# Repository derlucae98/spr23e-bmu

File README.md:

# spr23e-bmu
Disclaimer: This project is free to use. However, if you plan to use it at an official Formula Student event you have to clearly state the origin of the project in your presentation of the Engeneering Design Event! This project contains lethal voltages. You use this project at your own risk! Neither I nor the Scuderia Mensa will take any responsibility in case of damage, fire, injury or death.

Battery Management Unit for the Scuderia Mensa SPR23e/SPR24e electric race car.

REV B has been successfully tested. Rendering: 

The documentation is still in progress and far from finished. Firmare can be found here: https://github.com/derlucae98/spr-bmu-firmware

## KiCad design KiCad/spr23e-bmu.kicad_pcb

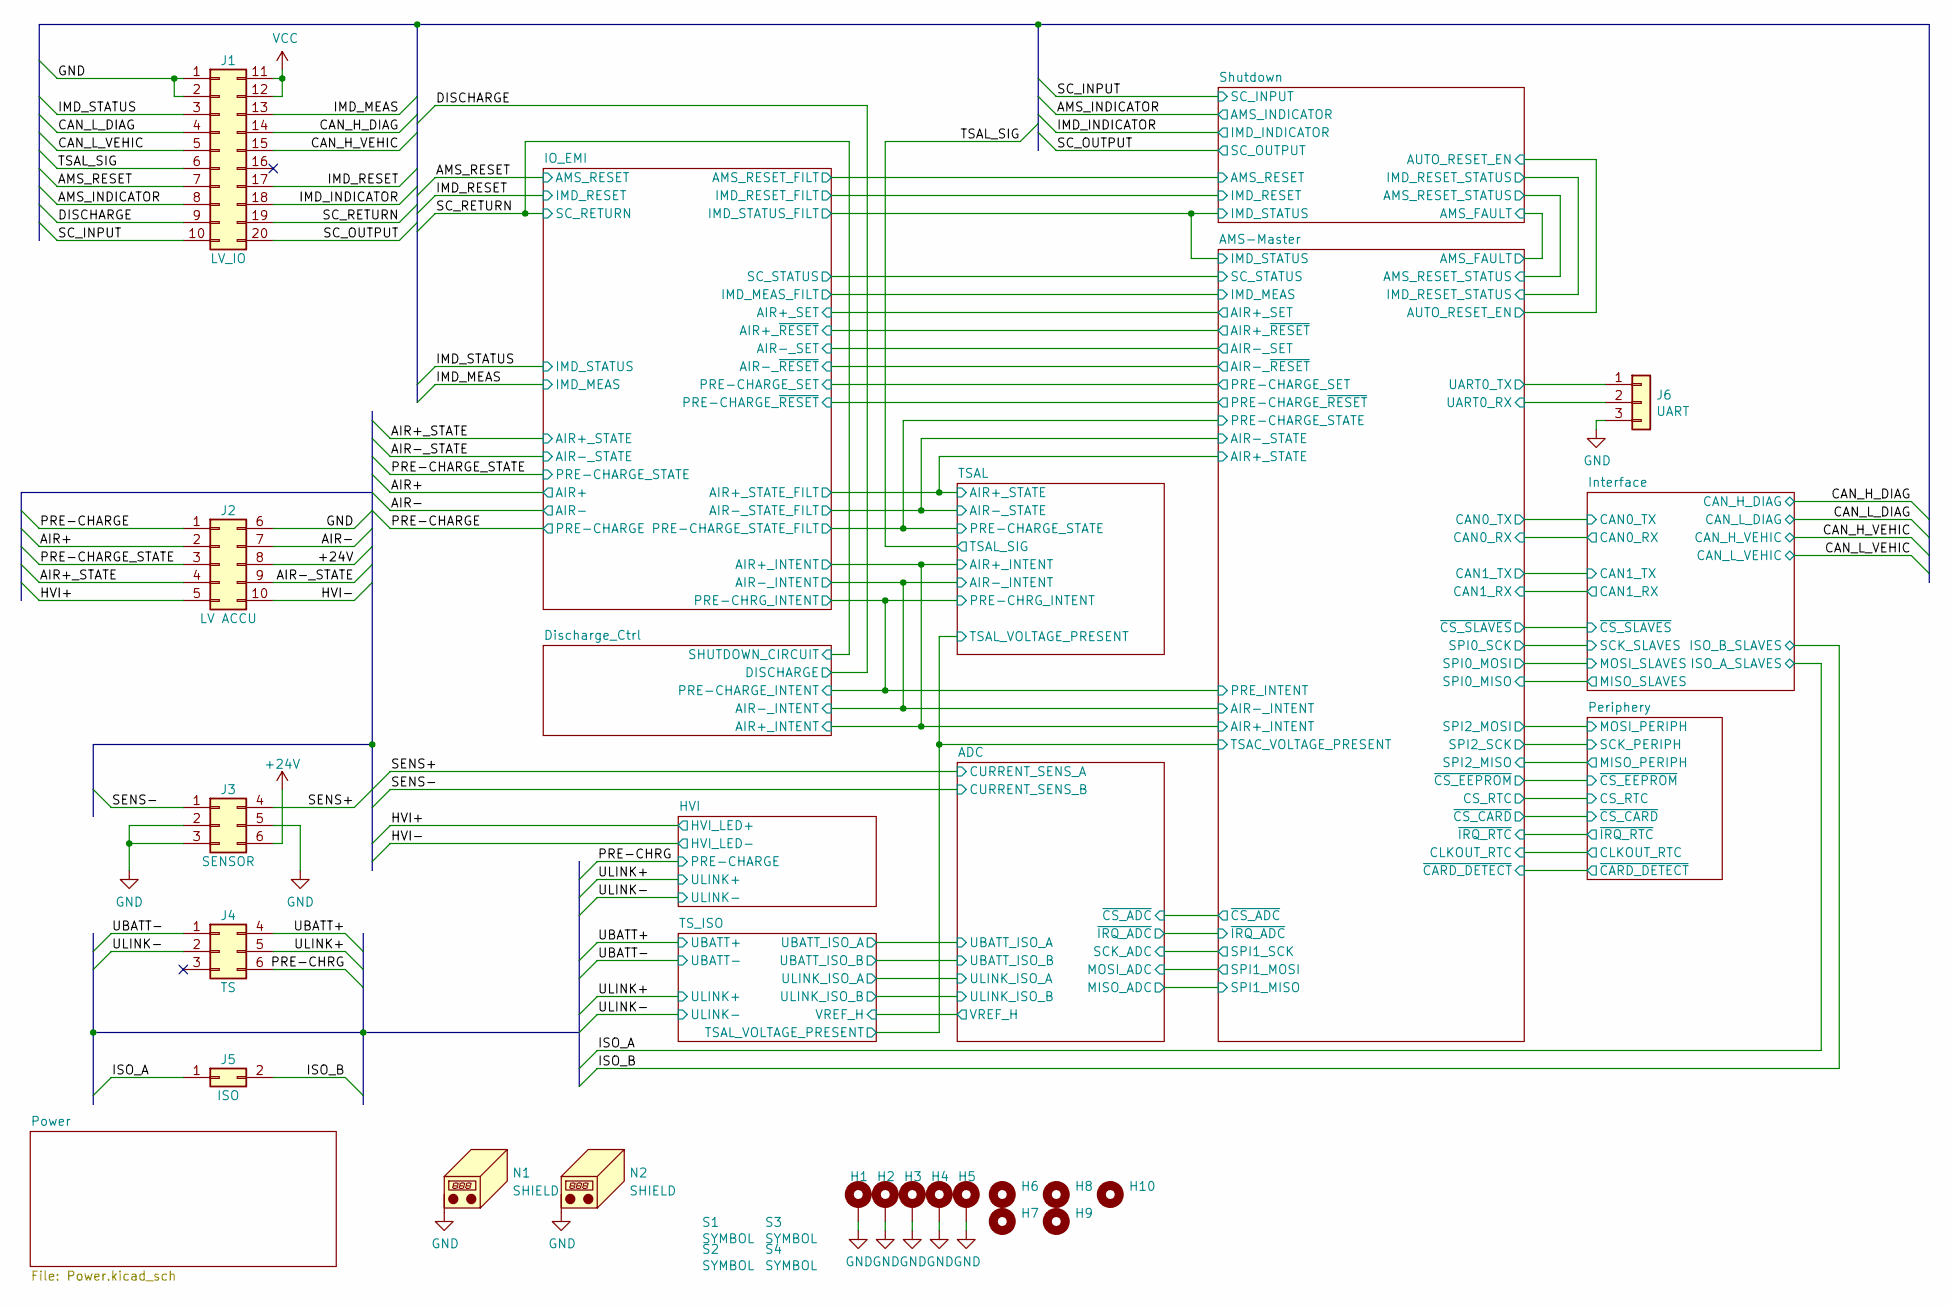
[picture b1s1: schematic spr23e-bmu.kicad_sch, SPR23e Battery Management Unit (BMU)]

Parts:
H1, H2, H3, H4, H5: MountingHole_4.3mm_M4_Pad_Via
H6, H7, H8, H9, H10: MountingHole_4.3mm_M4_ISO14580
J1: LV_IO; Molex_Micro-Fit_3.0_43045-2000_2x10_P3.00mm_Horizontal
J2: LV ACCU; Molex_Micro-Fit_3.0_43045-1000_2x05_P3.00mm_Horizontal
J3: SENSOR; Molex_Micro-Fit_3.0_43045-0600_2x03_P3.00mm_Horizontal
J4: TS; Molex_Micro-Fit_3.0_43045-0600_2x03_P3.00mm_Horizontal
J5: ISO; Molex_Micro-Fit_3.0_43045-0200_2x01_P3.00mm_Horizontal
J6: UART; PinHeader_1x03_P2.54mm_Vertical
N1, N2: SHIELD; SHIELD_FINGER_TE_1734303-1
S1: SYMBOL; Scuderia-Logo-Klein
S2: SYMBOL; Wappen-klein
S3, S4: SYMBOL; HV_WARNING_SMALL

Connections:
+24V: J2.8, J3.6; also elsewhere on the board
/AIR+: J2.2; also elsewhere on the board
/AIR+_STATE: J2.4; also elsewhere on the board
/AIR-: J2.7; also elsewhere on the board
/AIR-_STATE: J2.9; also elsewhere on the board
/AMS-Master/UART0_RX: J6.2; also elsewhere on the board
/AMS-Master/UART0_TX: J6.1; also elsewhere on the board
/AMS_INDICATOR: J1.8; also elsewhere on the board
/AMS_RESET: J1.7; also elsewhere on the board
/CAN_H_DIAG: J1.14; also elsewhere on the board
/CAN_H_VEHIC: J1.15; also elsewhere on the board
/CAN_L_DIAG: J1.4; also elsewhere on the board
/CAN_L_VEHIC: J1.5; also elsewhere on the board
/DISCHARGE: J1.9; also elsewhere on the board
/HVI+: J2.5; also elsewhere on the board
/IMD_INDICATOR: J1.18; also elsewhere on the board
/IMD_MEAS: J1.13; also elsewhere on the board
/IMD_RESET: J1.17; also elsewhere on the board
/IMD_STATUS: J1.3; also elsewhere on the board
/ISO_A: J5.1; also elsewhere on the board
/ISO_B: J5.2; also elsewhere on the board
/PRE-CHARGE: J2.1; also elsewhere on the board
/PRE-CHARGE_STATE: J2.3; also elsewhere on the board
/PRE-CHRG: J4.6; also elsewhere on the board
/SC_INPUT: J1.10; also elsewhere on the board
/SC_OUTPUT: J1.20; also elsewhere on the board
/SC_RETURN: J1.19; also elsewhere on the board
/SENS+: J3.4; also elsewhere on the board
/SENS-: J3.1; also elsewhere on the board
/TSAL_SIG: J1.6; also elsewhere on the board
/UBATT+: J4.4; also elsewhere on the board
/ULINK+: J4.5; also elsewhere on the board
GND: H1.1, H2.1, H3.1, H4.1, H5.1, J1.1, J1.2, J2.6, J2.10, J3.2, J3.3, J3.5, J6.3, N1.1 (PAD), N2.1 (PAD); also elsewhere on the board
GND1: J4.1; also elsewhere on the board
GND2: J4.2; also elsewhere on the board
VCC: J1.11, J1.12; also elsewhere on the board

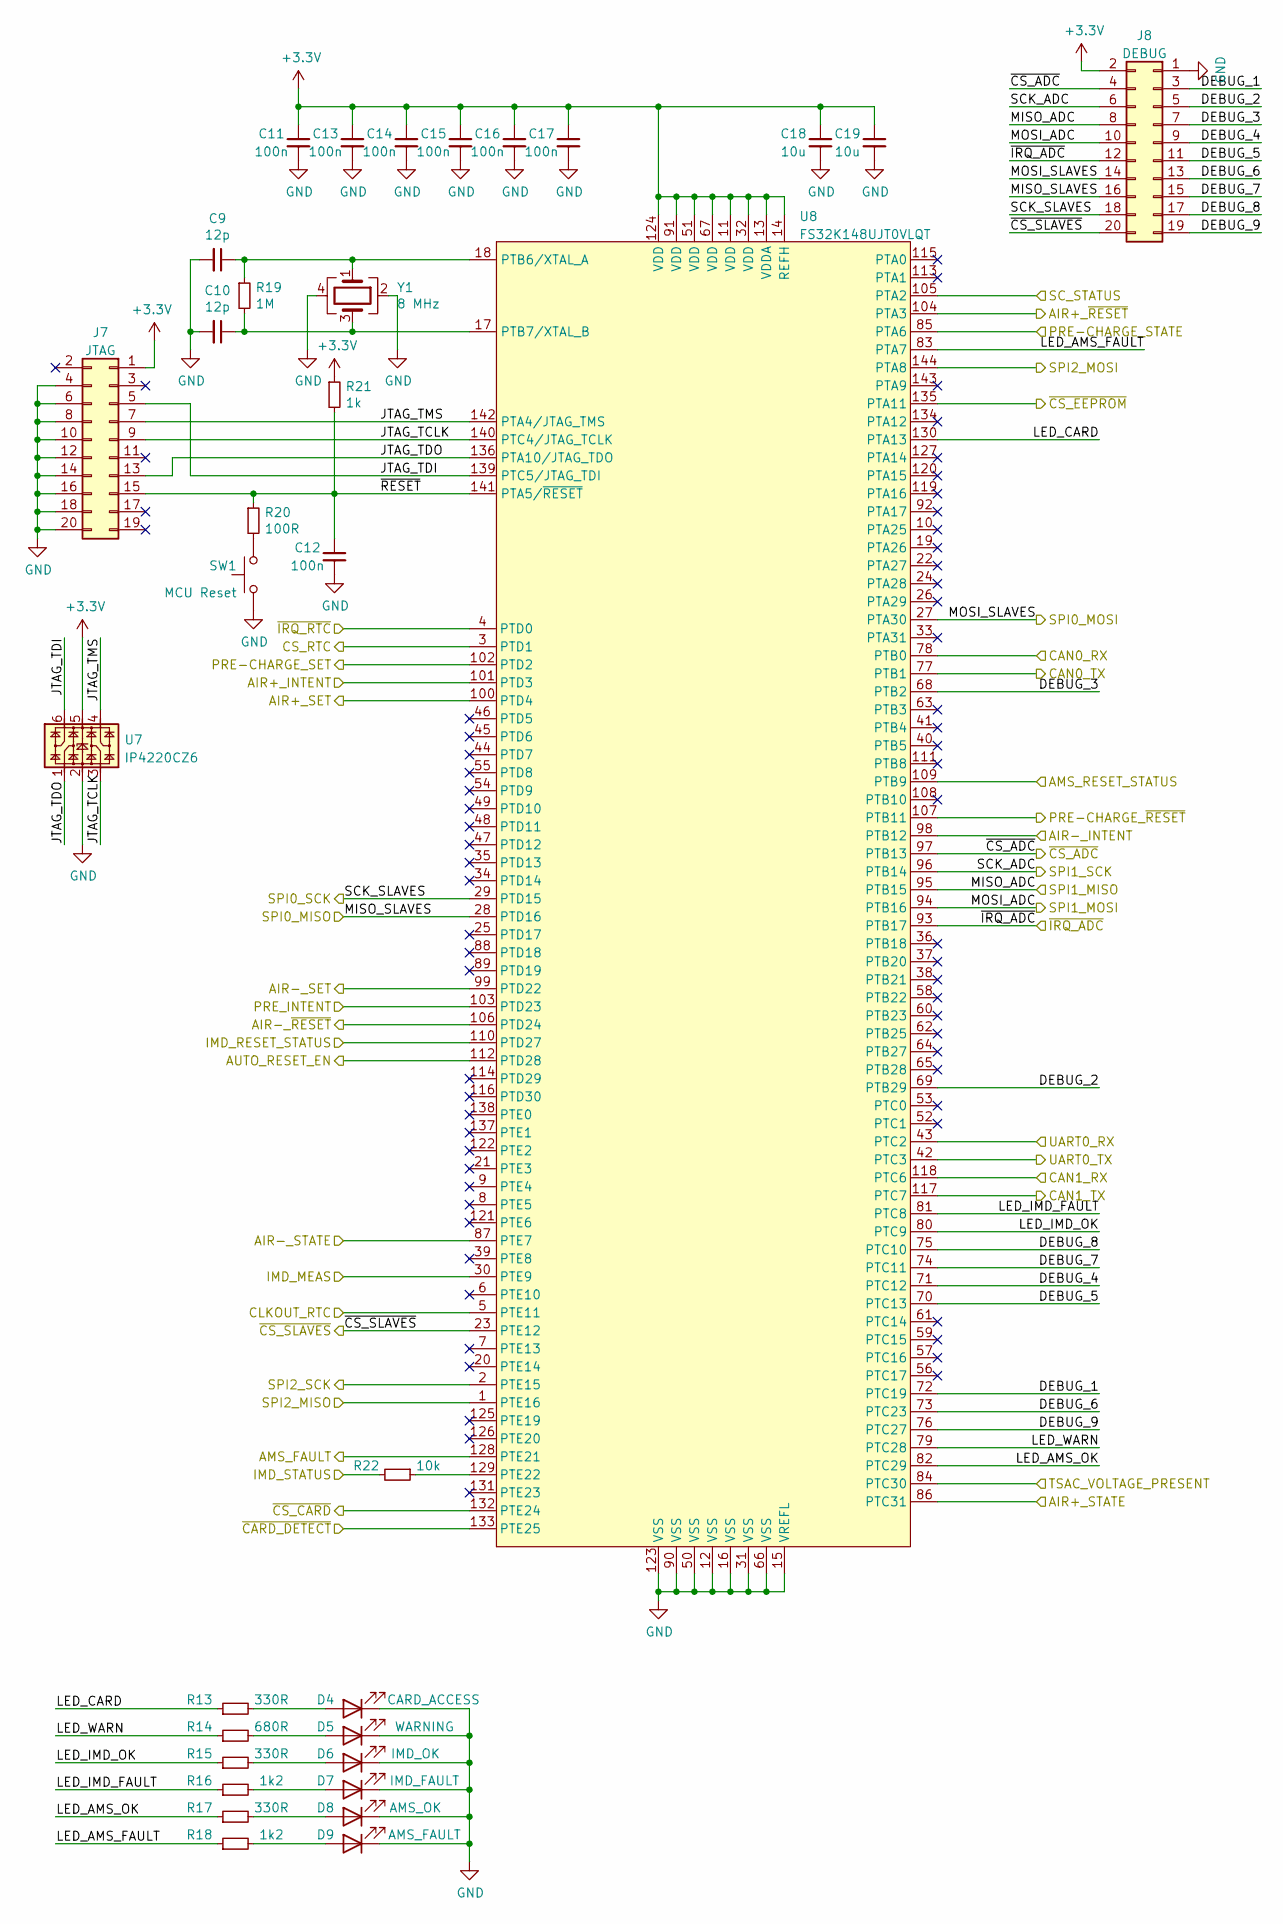
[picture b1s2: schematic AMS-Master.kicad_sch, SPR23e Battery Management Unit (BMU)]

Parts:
C9, C10: 12p; C_0603_1608Metric
C11, C12, C13, C14, C15, C16, C17: 100n; C_0603_1608Metric
C18, C19: 10u; C_1206_3216Metric
D4: CARD_ACCESS; LED_0603_1608Metric
D5: WARNING; LED_0603_1608Metric
D6: IMD_OK; LED_0603_1608Metric
D7: IMD_FAULT; LED_0603_1608Metric
D8: AMS_OK; LED_0603_1608Metric
D9: AMS_FAULT; LED_0603_1608Metric
J7: JTAG; IDC-Header_2x10_P2.54mm_Horizontal
J8: DEBUG; PinHeader_2x10_P2.54mm_Vertical
R13, R15, R17: 330R; R_0603_1608Metric
R14: 680R; R_0603_1608Metric
R16, R18: 1k2; R_0603_1608Metric
R19: 1M; R_0603_1608Metric
R20: 100R; R_0603_1608Metric
R21: 1k; R_0603_1608Metric
R22: 10k; R_0603_1608Metric
SW1: MCU Reset; SW_Push_1P1T_NO_6x6mm_H9.5mm
U7: IP4220CZ6; SOT-363_SC-70-6
U8: FS32K148UJT0VLQT; LQFP-144_20x20mm_P0.5mm
Y1: 8 MHz; Crystal_SMD_SeikoEpson_FA238V-4Pin_3.2x2.5mm

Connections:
+3.3V: C11.1, C13.1, C14.1, C15.1, C16.1, C17.1, C18.1, C19.1, J7.1, J8.2, R21.1, U7.5, U8.11 (VDD), U8.13 (VDDA), U8.14 (REFH), U8.32 (VDD), U8.51 (VDD), U8.67 (VDD), U8.91 (VDD), U8.124 (VDD); also elsewhere on the board
/AMS-Master/AIR+_INTENT: U8.101 (PTD3); also elsewhere on the board
/AMS-Master/AIR+_SET: U8.100 (PTD4); also elsewhere on the board
/AMS-Master/AIR+_STATE: U8.86 (PTC31); also elsewhere on the board
/AMS-Master/AIR+_~RESET: U8.104 (PTA3); also elsewhere on the board
/AMS-Master/AIR-_INTENT: U8.98 (PTB12); also elsewhere on the board
/AMS-Master/AIR-_SET: U8.99 (PTD22); also elsewhere on the board
/AMS-Master/AIR-_STATE: U8.87 (PTE7); also elsewhere on the board
/AMS-Master/AIR-_~RESET: U8.106 (PTD24); also elsewhere on the board
/AMS-Master/AMS_FAULT: U8.128 (PTE21); also elsewhere on the board
/AMS-Master/AMS_RESET_STATUS: U8.109 (PTB9); also elsewhere on the board
/AMS-Master/AUTO_RESET_EN: U8.112 (PTD28); also elsewhere on the board
/AMS-Master/CAN0_RX: U8.78 (PTB0); also elsewhere on the board
/AMS-Master/CAN0_TX: U8.77 (PTB1); also elsewhere on the board
/AMS-Master/CAN1_RX: U8.118 (PTC6); also elsewhere on the board
/AMS-Master/CAN1_TX: U8.117 (PTC7); also elsewhere on the board
/AMS-Master/CLKOUT_RTC: U8.5 (PTE11); also elsewhere on the board
/AMS-Master/CS_RTC: U8.3 (PTD1); also elsewhere on the board
/AMS-Master/DEBUG_1: J8.3, U8.72 (PTC19)
/AMS-Master/DEBUG_2: J8.5, U8.69 (PTB29)
/AMS-Master/DEBUG_3: J8.7, U8.68 (PTB2)
/AMS-Master/DEBUG_4: J8.9, U8.71 (PTC12)
/AMS-Master/DEBUG_5: J8.11, U8.70 (PTC13)
/AMS-Master/DEBUG_6: J8.13, U8.73 (PTC23)
/AMS-Master/DEBUG_7: J8.15, U8.74 (PTC11)
/AMS-Master/DEBUG_8: J8.17, U8.75 (PTC10)
/AMS-Master/DEBUG_9: J8.19, U8.76 (PTC27)
/AMS-Master/IMD_MEAS: U8.30 (PTE9); also elsewhere on the board
/AMS-Master/IMD_RESET_STATUS: U8.110 (PTD27); also elsewhere on the board
/AMS-Master/IMD_STATUS: R22.2; also elsewhere on the board
/AMS-Master/JTAG_TCLK: J7.9, U7.3, U8.140 (PTC4/JTAG_TCLK)
/AMS-Master/JTAG_TDI: J7.5, U7.6, U8.139 (PTC5/JTAG_TDI)
/AMS-Master/JTAG_TDO: J7.13, U7.1, U8.136 (PTA10/JTAG_TDO)
/AMS-Master/JTAG_TMS: J7.7, U7.4, U8.142 (PTA4/JTAG_TMS)
/AMS-Master/LED_AMS_FAULT: R18.1, U8.83 (PTA7)
/AMS-Master/LED_AMS_OK: R17.1, U8.82 (PTC29)
/AMS-Master/LED_CARD: R13.1, U8.130 (PTA13)
/AMS-Master/LED_IMD_FAULT: R16.1, U8.81 (PTC8)
/AMS-Master/LED_IMD_OK: R15.1, U8.80 (PTC9)
/AMS-Master/LED_WARN: R14.1, U8.79 (PTC28)
/AMS-Master/MISO_ADC: J8.8, U8.95 (PTB15); also elsewhere on the board
/AMS-Master/MISO_SLAVES: J8.16, U8.28 (PTD16); also elsewhere on the board
/AMS-Master/MOSI_ADC: J8.10, U8.94 (PTB16); also elsewhere on the board
/AMS-Master/MOSI_SLAVES: J8.14, U8.27 (PTA30); also elsewhere on the board
/AMS-Master/PRE-CHARGE_SET: U8.102 (PTD2); also elsewhere on the board
/AMS-Master/PRE-CHARGE_STATE: U8.85 (PTA6); also elsewhere on the board
/AMS-Master/PRE-CHARGE_~RESET: U8.107 (PTB11); also elsewhere on the board
/AMS-Master/PRE_INTENT: U8.103 (PTD23); also elsewhere on the board
/AMS-Master/SCK_ADC: J8.6, U8.96 (PTB14); also elsewhere on the board
/AMS-Master/SCK_SLAVES: J8.18, U8.29 (PTD15); also elsewhere on the board
/AMS-Master/SC_STATUS: U8.105 (PTA2); also elsewhere on the board
/AMS-Master/SPI2_MISO: U8.1 (PTE16); also elsewhere on the board
/AMS-Master/SPI2_MOSI: U8.144 (PTA8); also elsewhere on the board
/AMS-Master/SPI2_SCK: U8.2 (PTE15); also elsewhere on the board
/AMS-Master/TSAC_VOLTAGE_PRESENT: U8.84 (PTC30); also elsewhere on the board
/AMS-Master/UART0_RX: U8.43 (PTC2); also elsewhere on the board
/AMS-Master/UART0_TX: U8.42 (PTC3); also elsewhere on the board
/AMS-Master/~CARD_DETECT: U8.133 (PTE25); also elsewhere on the board
/AMS-Master/~CS_ADC: J8.4, U8.97 (PTB13); also elsewhere on the board
/AMS-Master/~CS_CARD: U8.132 (PTE24); also elsewhere on the board
/AMS-Master/~CS_EEPROM: U8.135 (PTA11); also elsewhere on the board
/AMS-Master/~CS_SLAVES: J8.20, U8.23 (PTE12); also elsewhere on the board
/AMS-Master/~IRQ_ADC: J8.12, U8.93 (PTB17); also elsewhere on the board
/AMS-Master/~IRQ_RTC: U8.4 (PTD0); also elsewhere on the board
/AMS-Master/~RESET: C12.1, J7.15, R20.1, R21.2, U8.141 (PTA5/~RESET)
GND: C9.2, C10.2, C11.2, C12.2, C13.2, C14.2, C15.2, C16.2, C17.2, C18.2, C19.2, D4.1 (K), D5.1 (K), D6.1 (K), D7.1 (K), D8.1 (K), D9.1 (K), J7.4, J7.6, J7.8, J7.10, J7.12, J7.14, J7.16, J7.18, J7.20, J8.1, SW1.1, U7.2, U8.12 (VSS), U8.15 (VREFL), U8.16 (VSS), U8.31 (VSS), U8.50 (VSS), U8.66 (VSS), U8.90 (VSS), U8.123 (VSS), Y1.2, Y1.4; also elsewhere on the board
unnamed: D4.2 (A), R13.2
unnamed: D5.2 (A), R14.2
unnamed: D6.2 (A), R15.2
unnamed: D7.2 (A), R16.2
unnamed: D8.2 (A), R17.2
unnamed: D9.2 (A), R18.2
unnamed: R20.2, SW1.2
unnamed: C9.1, R19.1, U8.18 (PTB6/XTAL_A), Y1.1
unnamed: C10.1, R19.2, U8.17 (PTB7/XTAL_B), Y1.3
unnamed: R22.1, U8.129 (PTE22)

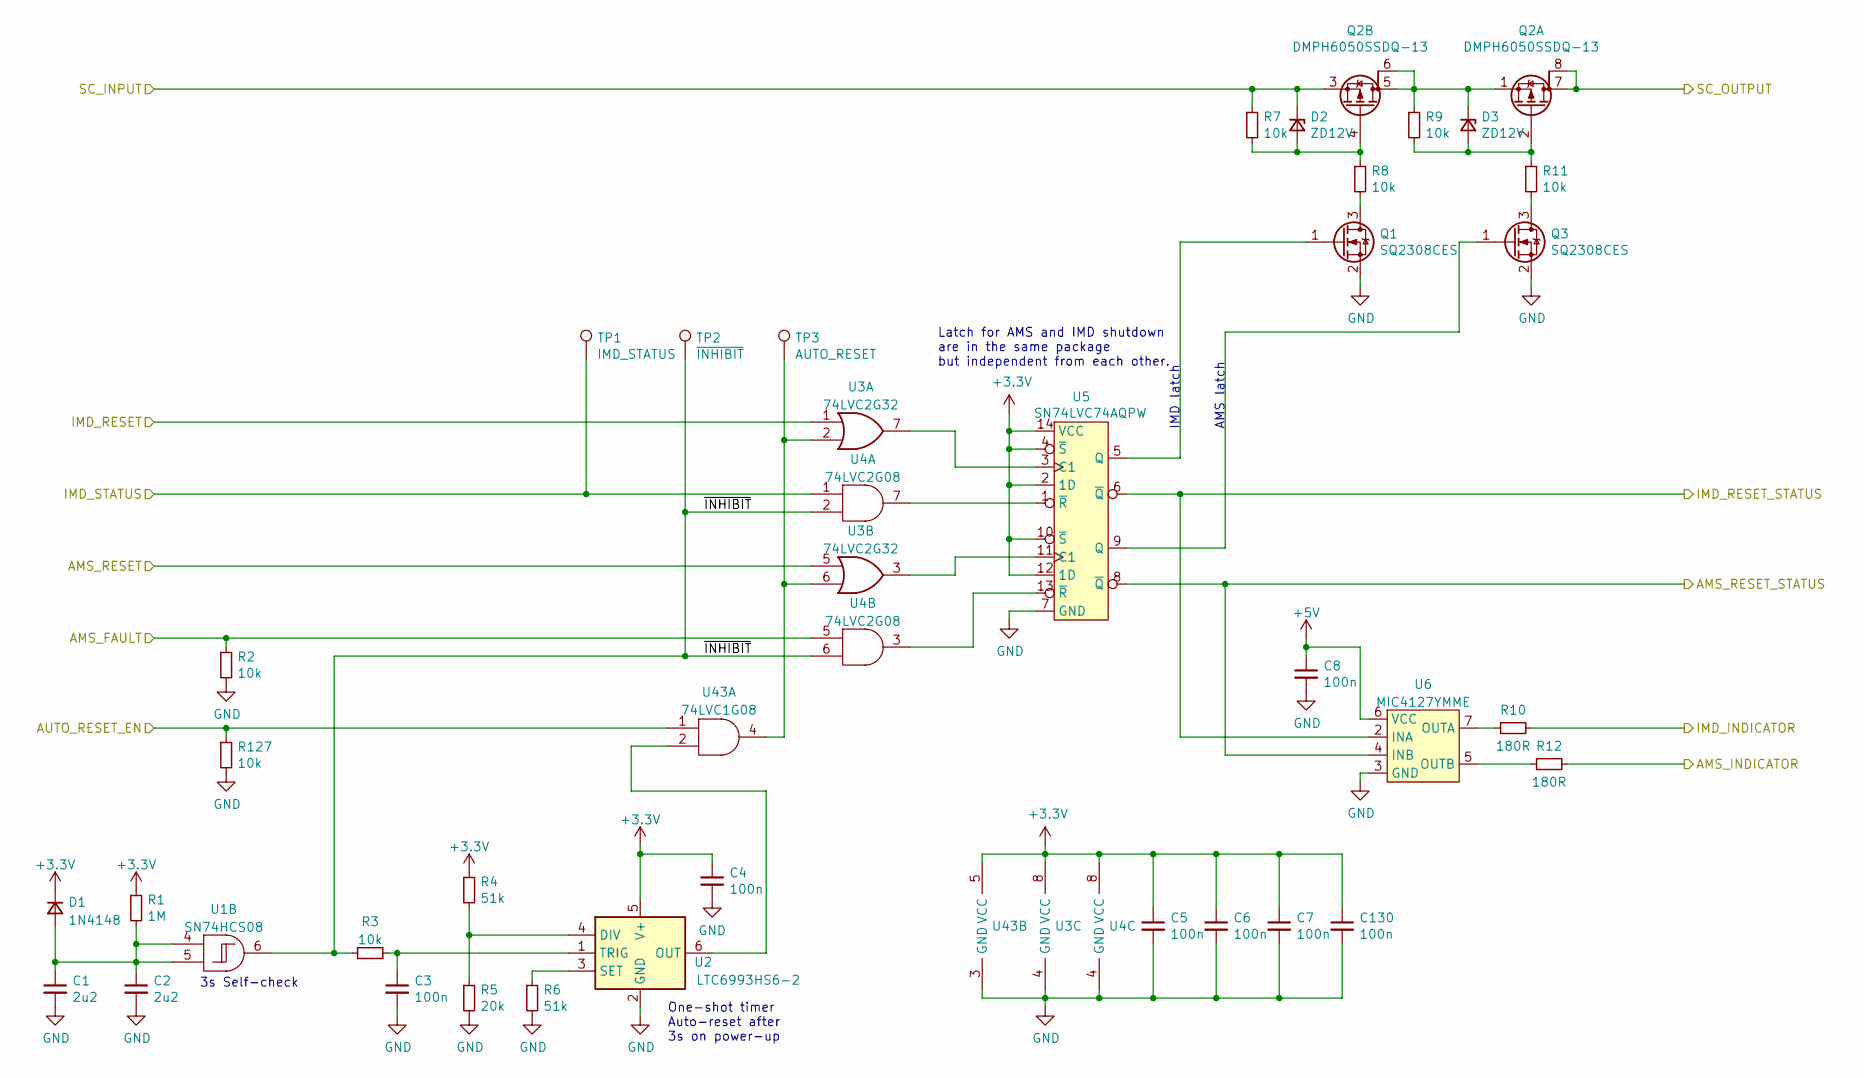
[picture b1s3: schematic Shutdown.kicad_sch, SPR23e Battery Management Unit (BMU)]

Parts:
C1, C2: 2u2; C_0805_2012Metric
C3, C4, C5, C6, C7, C8, C130: 100n; C_0603_1608Metric
D1: 1N4148; D_SOD-123
D2, D3: ZD12V; D_SOD-123
Q1, Q3: SQ2308CES; SOT-23
Q2: DMPH6050SSDQ-13; SOIC-8_3.9x4.9mm_P1.27mm
R1: 1M; R_0603_1608Metric
R2, R3, R7, R8, R9, R11, R127: 10k; R_0603_1608Metric
R4, R6: 51k; R_0603_1608Metric
R5: 20k; R_0603_1608Metric
R10, R12: 180R; R_0603_1608Metric
TP1: IMD_STATUS; TestPoint_Pad_D1.5mm
TP2: ~{INHIBIT}; TestPoint_Pad_D1.5mm
TP3: AUTO_RESET; TestPoint_Pad_D1.5mm
U1: SN74HCS08; TSSOP-14_4.4x5mm_P0.65mm
U2: LTC6993HS6-2; TSOT-23-6
U3: 74LVC2G32; VSSOP-8_2.4x2.1mm_P0.5mm
U4: 74LVC2G08; VSSOP-8_2.4x2.1mm_P0.5mm
U5: SN74LVC74AQPW; TSSOP-14_4.4x5mm_P0.65mm
U6: MIC4127YMME; MSOP-8-1EP_3x3mm_P0.65mm_EP1.95x2.15mm_ThermalVias
U43: 74LVC1G08; SOT-23-5

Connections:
+3.3V: C4.1, C5.1, C6.1, C7.1, C130.1, D1.1 (K), R1.1, R4.1, U2.5 (V+), U3.8 (VCC), U4.8 (VCC), U5.2 (1D), U5.4 (~S), U5.10 (~S), U5.12 (1D), U5.14 (VCC), U43.5 (VCC); also elsewhere on the board
+5V: C8.1, U6.6 (VCC); also elsewhere on the board
/AMS-Master/AMS_FAULT: R2.1, U4.5; also elsewhere on the board
/AMS-Master/AMS_RESET_STATUS: U5.8 (~Q), U6.4 (INB); also elsewhere on the board
/AMS-Master/AUTO_RESET_EN: R127.1, U43.1; also elsewhere on the board
/AMS-Master/IMD_RESET_STATUS: U5.6 (~Q), U6.2 (INA); also elsewhere on the board
/AMS-Master/IMD_STATUS: TP1.1, U4.1; also elsewhere on the board
/AMS_INDICATOR: R12.2; also elsewhere on the board
/IMD_INDICATOR: R10.2; also elsewhere on the board
/IO_EMI/AMS_RESET_FILT: U3.5; also elsewhere on the board
/IO_EMI/IMD_RESET_FILT: U3.1; also elsewhere on the board
/SC_INPUT: D2.1 (K), Q2.3 (S), R7.1; also elsewhere on the board
/SC_OUTPUT: Q2.7 (D), Q2.8 (G); also elsewhere on the board
/Shutdown/~INHIBIT: R3.1, TP2.1, U1.6, U4.2, U4.6
GND: C1.2, C2.2, C3.2, C4.2, C5.2, C6.2, C7.2, C8.2, C130.2, Q1.2 (S), Q3.2 (S), R2.2, R5.2, R6.2, R127.2, U2.2 (GND), U3.4 (GND), U4.4 (GND), U5.7 (GND), U6.3 (GND), U6.9 (GND), U43.3 (GND); also elsewhere on the board
unnamed: C1.1, C2.1, D1.2 (A), R1.2, U1.4, U1.5
unnamed: D2.2 (A), Q2.4 (G), R7.2, R8.1
unnamed: D3.2 (A), Q2.2 (G), R9.2, R11.1
unnamed: D3.1 (K), Q2.1 (S), Q2.5 (D), Q2.6 (G), R9.1
unnamed: Q1.3 (D), R8.2
unnamed: Q1.1 (G), U5.5 (Q)
unnamed: Q3.3 (D), R11.2
unnamed: Q3.1 (G), U5.9 (Q)
unnamed: TP3.1, U3.2, U3.6, U43.4
unnamed: R4.2, R5.1, U2.4 (DIV)
unnamed: U2.6 (OUT), U43.2
unnamed: R6.1, U2.3 (SET)
unnamed: C3.1, R3.2, U2.1 (TRIG)
unnamed: U3.3, U5.11 (C1)
unnamed: U3.7, U5.3 (C1)
unnamed: U4.3, U5.13 (~R)
unnamed: U4.7, U5.1 (~R)
unnamed: R10.1, U6.7 (OUTA)
unnamed: R12.1, U6.5 (OUTB)

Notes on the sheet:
Latch for AMS and IMD shutdown are in the same package but independent from each other.
3s Self-check
One-shot timer Auto-reset after 3s on power-up
AMS latch
IMD latch

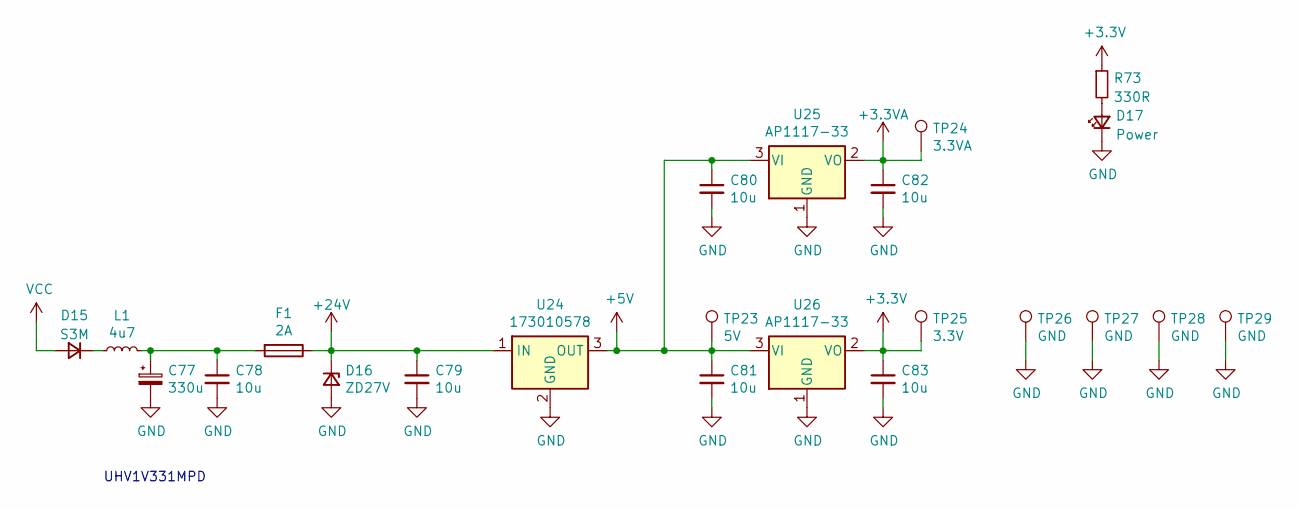
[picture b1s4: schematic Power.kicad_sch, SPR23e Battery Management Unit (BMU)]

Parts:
C77: 330u; CP_Radial_D10.0mm_P5.00mm
C78, C79, C80, C81, C82, C83: 10u; C_1206_3216Metric
D15: S3M; D_SMC
D16: ZD27V; D_SMB
D17: Power; LED_0603_1608Metric
F1: 2A; 0154xxxxxxx
L1: 4u7; L_1206_3216Metric
R73: 330R; R_0603_1608Metric
TP23: 5V; TestPoint_Keystone_5010-5014_Multipurpose
TP24: 3.3VA; TestPoint_Keystone_5010-5014_Multipurpose
TP25: 3.3V; TestPoint_Keystone_5010-5014_Multipurpose
TP26, TP27, TP28, TP29: GND; TestPoint_Keystone_5010-5014_Multipurpose
U24: 173010578; Converter_DCDC_TRACO_TSR-1_THT
U25, U26: AP1117-33; SOT-223-3_TabPin2

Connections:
+3.3V: C83.1, R73.1, TP25.1, U26.2 (VO); also elsewhere on the board
+3.3VA: C82.1, TP24.1, U25.2 (VO); also elsewhere on the board
+5V: C80.1, C81.1, TP23.1, U24.3 (OUT), U25.3 (VI), U26.3 (VI); also elsewhere on the board
+24V: C79.1, D16.1 (K), F1.1, U24.1 (IN); also elsewhere on the board
GND: C77.2, C78.2, C79.2, C80.2, C81.2, C82.2, C83.2, D16.2 (A), D17.1 (K), TP26.1, TP27.1, TP28.1, TP29.1, U24.2 (GND), U25.1 (GND), U26.1 (GND); also elsewhere on the board
unnamed: C77.1, C78.1, F1.2, L1.2
unnamed: D15.1 (K), L1.1
unnamed: D17.2 (A), R73.2
VCC: D15.2 (A); also elsewhere on the board

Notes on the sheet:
UHV1V331MPD

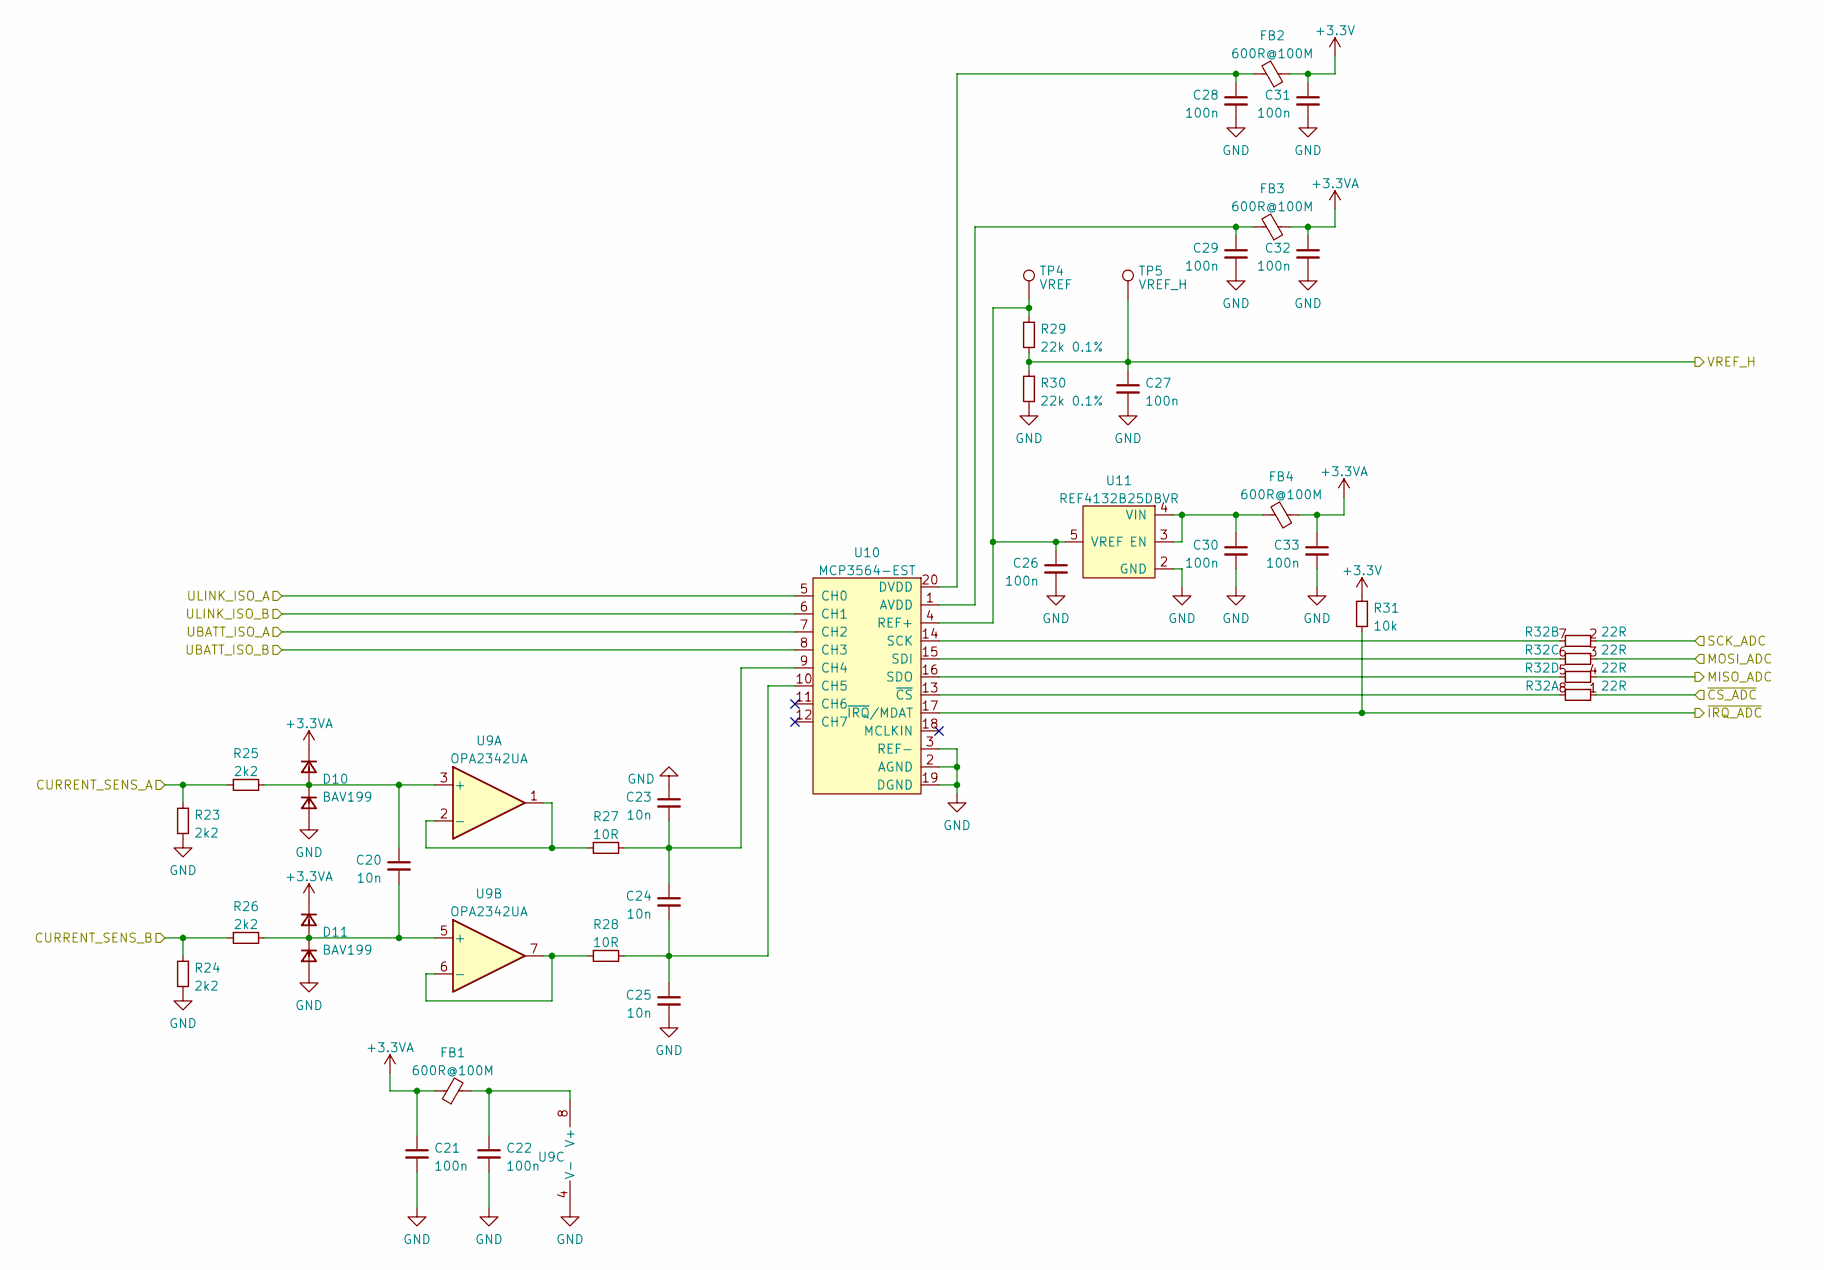
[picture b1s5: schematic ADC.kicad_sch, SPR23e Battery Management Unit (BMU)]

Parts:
C20, C23, C24, C25: 10n; C_0603_1608Metric
C21, C22, C26, C27, C28, C29, C30, C31, C32, C33: 100n; C_0603_1608Metric
D10, D11: BAV199; SOT-23
FB1, FB2, FB3, FB4: 600R@100M; L_0603_1608Metric
R23, R24, R25, R26: 2k2; R_0603_1608Metric
R27, R28: 10R; R_0603_1608Metric
R29, R30: 22k 0.1%; R_0603_1608Metric
R31: 10k; R_0603_1608Metric
R32: 22R; R_Array_Convex_4x0603
TP4: VREF; TestPoint_Pad_D1.5mm
TP5: VREF_H; TestPoint_Pad_D1.5mm
U9: OPA2342UA; SOIC-8_3.9x4.9mm_P1.27mm
U10: MCP3564-EST; TSSOP-20_4.4x6.5mm_P0.65mm
U11: REF4132B25DBVR; SOT-23-5

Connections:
+3.3V: C31.1, FB2.1, R31.1; also elsewhere on the board
+3.3VA: C21.1, C32.1, C33.1, D10.2 (K), D11.2 (K), FB1.1, FB3.1, FB4.1; also elsewhere on the board
/ADC/UBATT_ISO_A: U10.7 (CH2); also elsewhere on the board
/ADC/UBATT_ISO_B: U10.8 (CH3); also elsewhere on the board
/ADC/ULINK_ISO_A: U10.5 (CH0); also elsewhere on the board
/ADC/ULINK_ISO_B: U10.6 (CH1); also elsewhere on the board
/ADC/VREF_H: C27.1, R29.2, R30.1, TP5.1; also elsewhere on the board
/AMS-Master/MISO_ADC: R32.4; also elsewhere on the board
/AMS-Master/MOSI_ADC: R32.3; also elsewhere on the board
/AMS-Master/SCK_ADC: R32.2; also elsewhere on the board
/AMS-Master/~CS_ADC: R32.1; also elsewhere on the board
/AMS-Master/~IRQ_ADC: R31.2, U10.17 (~IRQ/MDAT); also elsewhere on the board
/SENS+: R23.1, R25.1; also elsewhere on the board
/SENS-: R24.1, R26.1; also elsewhere on the board
GND: C21.2, C22.2, C23.1, C25.2, C26.2, C27.2, C28.2, C29.2, C30.2, C31.2, C32.2, C33.2, D10.1 (A), D11.1 (A), R23.2, R24.2, R30.2, U9.4 (V-), U10.2 (AGND), U10.3 (REF-), U10.19 (DGND), U11.2 (GND); also elsewhere on the board
unnamed: C20.1, D10.3 (K), R25.2, U9.3 (+)
unnamed: R27.1, U9.1, U9.2 (-)
unnamed: C20.2, D11.3 (K), R26.2, U9.5 (+)
unnamed: R28.1, U9.6 (-), U9.7
unnamed: C22.1, FB1.2, U9.8 (V+)
unnamed: C29.1, FB3.2, U10.1 (AVDD)
unnamed: C23.2, C24.1, R27.2, U10.9 (CH4)
unnamed: C24.2, C25.1, R28.2, U10.10 (CH5)
unnamed: C28.1, FB2.2, U10.20 (DVDD)
unnamed: C26.1, R29.1, TP4.1, U10.4 (REF+), U11.5 (VREF)
unnamed: R32.7, U10.14 (SCK)
unnamed: R32.6, U10.15 (SDI)
unnamed: R32.5, U10.16 (SDO)
unnamed: R32.8, U10.13 (~CS)
unnamed: C30.1, FB4.2, U11.3 (EN), U11.4 (VIN)
